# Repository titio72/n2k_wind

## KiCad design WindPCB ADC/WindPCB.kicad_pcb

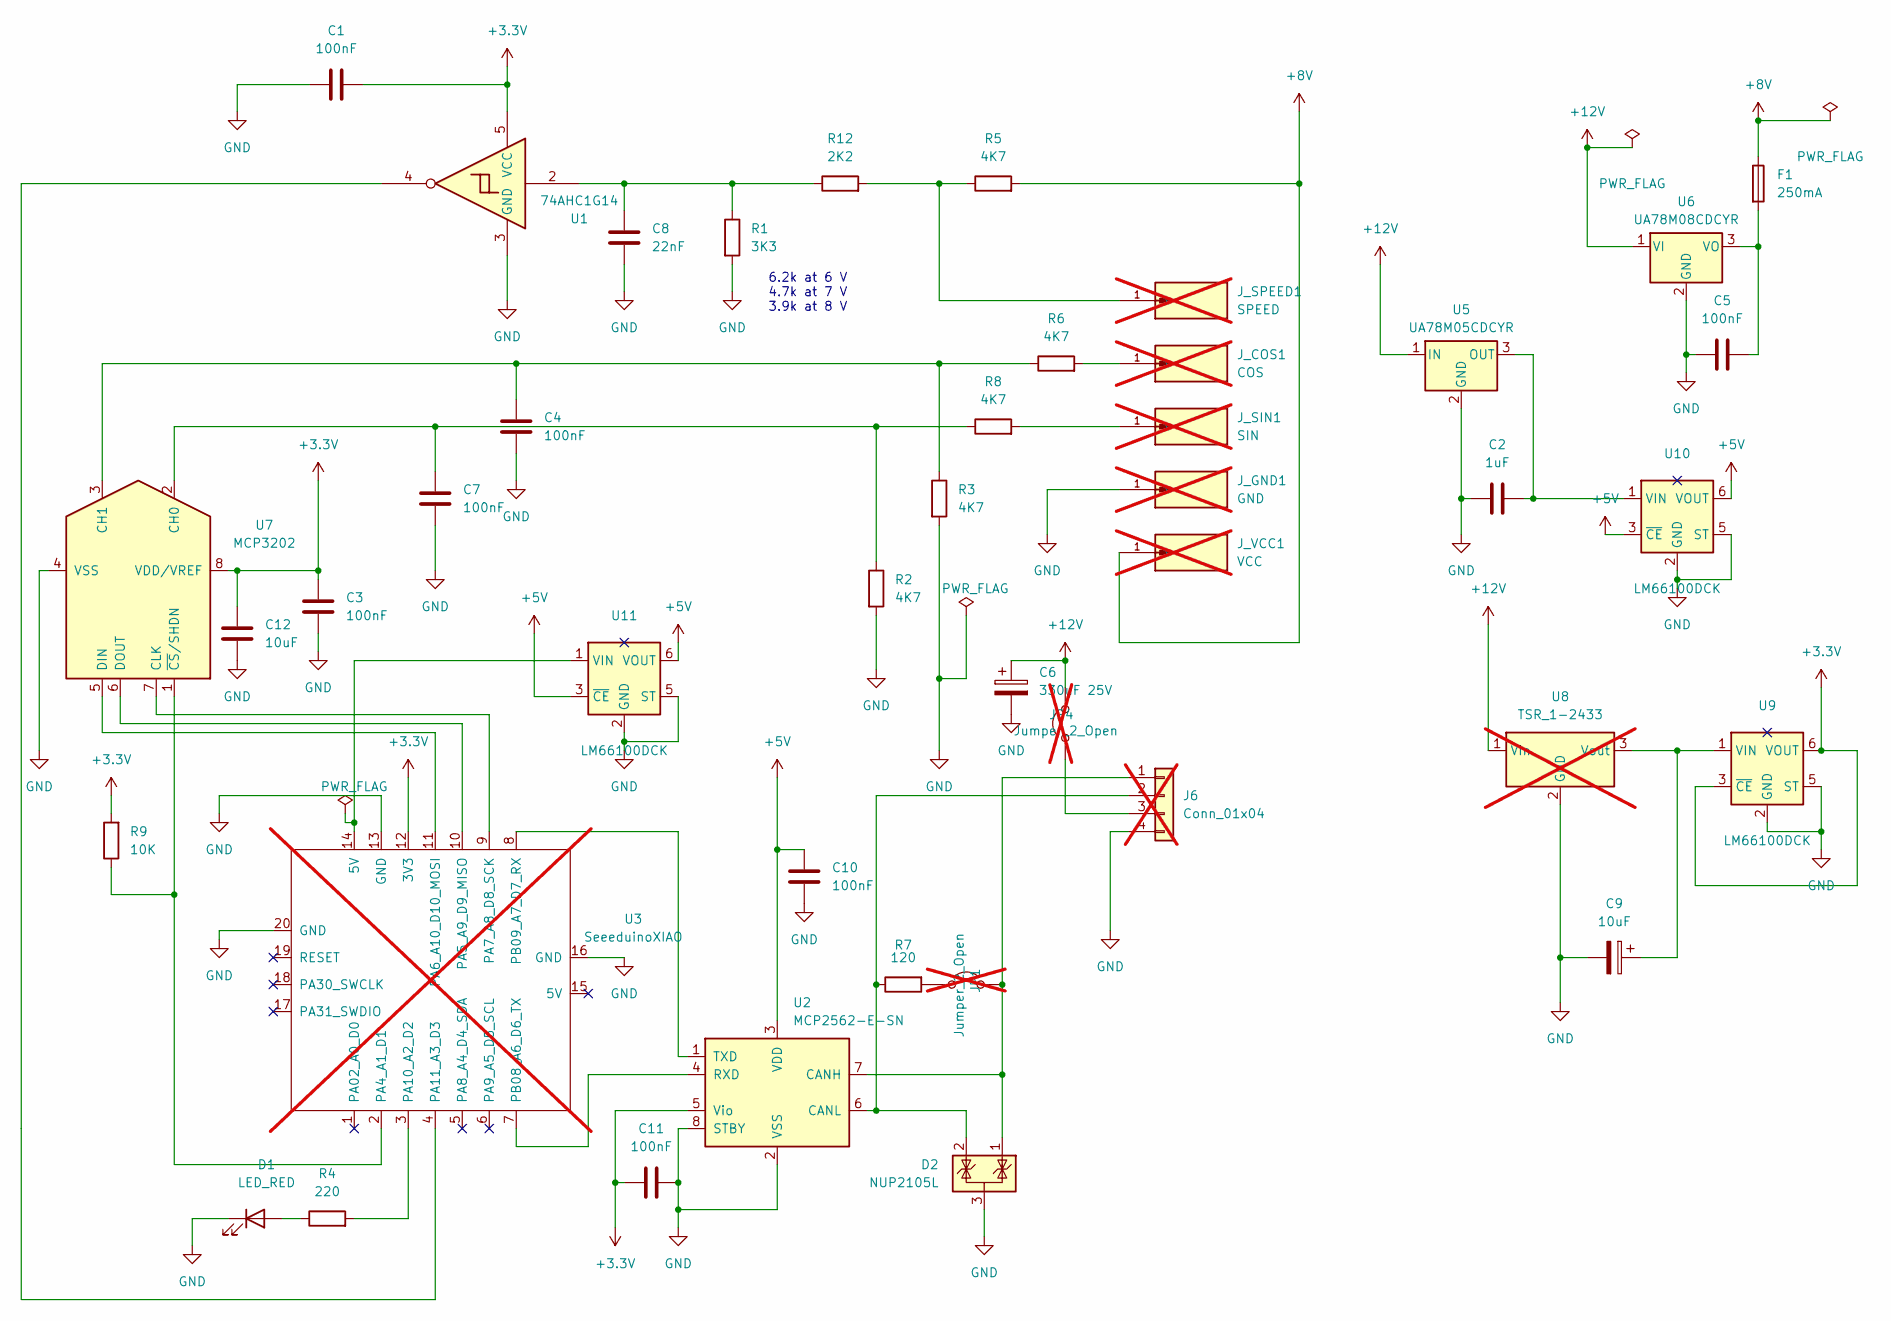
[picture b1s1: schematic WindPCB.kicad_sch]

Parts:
C1, C3, C4, C5, C7, C10, C11: 100nF; C_0805_2012Metric; MPN CC0805KRX7R9BB104
C2: 1uF; C_0805_2012Metric; MPN CC0805KRX7R7BB105
C6: 330uF 25V; CP_Elec_8x10; MPN EEE-FK1E331P
C8: 22nF; C_0805_2012Metric; MPN CC0805KRX7R9BB223
C9: 10uF; CP_EIA-3216-18_Kemet-A; MPN T491A106K010AT
C12: 10uF; C_0805_2012Metric; MPN CL21A106KOQNNNE
D1: LED_RED; LED_0805_2012Metric; MPN 150080RS75000
D2: NUP2105L; SOT-23; MPN NUP2105LT1G
F1: 250mA; Fuse_Littelfuse-NANO2-451_453; MPN 0454.250MR
J6: Conn_01x04; JST_EH_B4B-EH-A_1x04_P2.50mm_Vertical; not fitted
JP1, JP4: Jumper_2_Open; PinHeader_1x02_P2.54mm_Vertical; not fitted
J_COS1: COS; KEYSTONE_1267; PARTREV D; not fitted
J_GND1: GND; KEYSTONE_1267; PARTREV D; not fitted
J_SIN1: SIN; KEYSTONE_1267; PARTREV D; not fitted
J_SPEED1: SPEED; KEYSTONE_1267; PARTREV D; not fitted
J_VCC1: VCC; KEYSTONE_1267; PARTREV D; not fitted
R1: 3K3; R_0805_2012Metric; MPN RC0805FR-073K3L
R2, R3, R5, R6, R8: 4K7; R_0805_2012Metric; MPN RC0805FR-074K7L
R4: 220; R_0805_2012Metric; MPN RC0805FR-07220RL
R7: 120; R_0805_2012Metric; MPN RC0805FR-07120RL
R9: 10K; R_0805_2012Metric; MPN RC0805FR-0710KL
R12: 2K2; R_0805_2012Metric; MPN RC0805FR-072K2L
U1: 74AHC1G14; SOT-23-5_HandSoldering; MPN SN74AHC1G14DBVR
U2: MCP2562-E-SN; SOIC-8_3.9x4.9mm_P1.27mm; MPN MCP2562-E/SN
U3: SeeeduinoXIAO; Seeeduino XIAO-MOUDLE14P-2.54-21X17.8MM_1; not fitted
U5: UA78M05CDCYR; SOT-223-3_TabPin2; MPN UA78M05CDCYR
U6: UA78M08CDCYR; SOT-223-3_TabPin2; MPN UA78M08CDCYR
U7: MCP3202; SOIC-8_3.9x4.9mm_P1.27mm; MPN MCP3202-CI/SN
U8: TSR_1-2433; Converter_DCDC_TRACO_TSR-1_THT; MPN TSR 1-2433; not fitted
U9, U10, U11: LM66100DCK; SOT-363_SC-70-6; MPN LM66100DCKR

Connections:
+3.3V: C1.1, C3.1, C11.1, C12.1, R9.2, U1.5 (VCC), U2.5 (Vio), U3.12 (3V3), U7.8 (VDD/VREF), U9.3 (~CE), U9.6 (VOUT)
+5V: C10.1, U2.3 (VDD), U10.3 (~CE), U10.6 (VOUT), U11.3 (~CE), U11.6 (VOUT)
+8V: F1.1, J_VCC1.1, R5.2
+12V: C6.1, JP4.2 (B), U5.1 (IN), U6.1 (VI), U8.1 (Vin)
GND: C1.2, C2.1, C3.2, C4.2, C5.1, C6.2, C7.2, C8.2, C9.2, C10.2, C11.2, C12.2, D1.1 (K), D2.3 (A), J6.4, J_GND1.1, R1.2, R2.2, R3.2, U1.3 (GND), U2.2 (VSS), U2.8 (STBY), U3.13 (GND), U3.16 (GND), U3.20 (GND), U5.2 (GND), U6.2 (GND), U7.4 (VSS), U8.2 (GND), U9.2 (GND), U9.5 (ST), U10.2 (GND), U10.5 (ST), U11.2 (GND), U11.5 (ST)
unnamed: C8.1, R1.1, R12.1, U1.2
unnamed: D1.2 (A), R4.1
unnamed: D2.1 (K), J6.1, JP1.2 (B), U2.7 (CANH)
unnamed: D2.2 (K), J6.2, R7.1, U2.6 (CANL)
unnamed: J6.3, JP4.1 (A)
unnamed: JP1.1 (A), R7.2
unnamed: J_COS1.1, R6.2
unnamed: J_SIN1.1, R8.2
unnamed: J_SPEED1.1, R5.1, R12.2
unnamed: U2.4 (RXD), U3.7 (PB08_A6_D6_TX)
unnamed: U2.1 (TXD), U3.8 (PB09_A7_D7_RX)
unnamed: R9.1, U3.2 (PA4_A1_D1), U7.1 (~CS/SHDN)
unnamed: U3.10 (PA5_A9_D9_MISO), U7.6 (DOUT)
unnamed: U3.11 (PA6_A10_D10_MOSI), U7.5 (DIN)
unnamed: U3.9 (PA7_A8_D8_SCK), U7.7 (CLK)
unnamed: R4.2, U3.3 (PA10_A2_D2)
unnamed: U1.4, U3.4 (PA11_A3_D3)
unnamed: C5.2, F1.2, U6.3 (VO)
unnamed: C7.1, R2.1, R8.1, U7.2 (CH0)
unnamed: C4.1, R3.1, R6.1, U7.3 (CH1)
unnamed: C9.1, U8.3 (Vout), U9.1 (VIN)
unnamed: C2.2, U5.3 (OUT), U10.1 (VIN)
unnamed: U3.14 (5V), U11.1 (VIN)

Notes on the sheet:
6.2k at 6 V 4.7k at 7 V 3.9k at 8 V

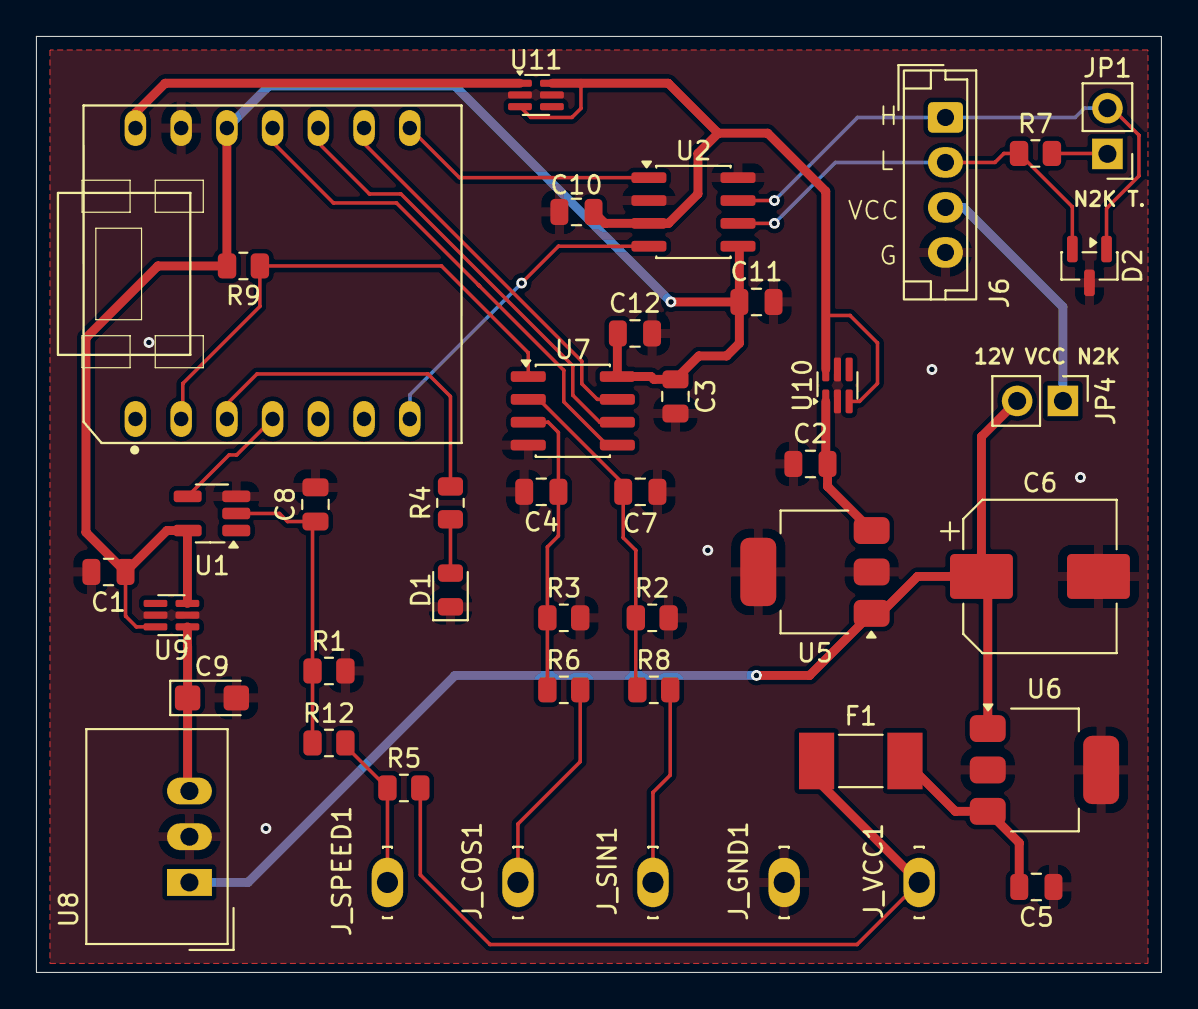
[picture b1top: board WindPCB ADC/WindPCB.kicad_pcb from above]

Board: 2 copper layers, 62.5 x 52.0 mm, 43 parts (0 on the bottom side), 28 nets.

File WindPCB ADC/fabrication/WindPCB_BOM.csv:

"Designator","Value","Footprint","Quantity","MPN","Manufacturer"
"C1, C3, C4, C5, C7, C10, C11","100nF","Capacitor_SMD:C_0805_2012Metric","7","CC0805KRX7R9BB104","Yageo"
"C2","1uF","Capacitor_SMD:C_0805_2012Metric","1","CC0805KRX7R7BB105","Yageo"
"C6","330uF 25V","Capacitor_SMD:CP_Elec_8x10","1","EEE-FK1E331P","Panasonic"
"C8","22nF","Capacitor_SMD:C_0805_2012Metric","1","CC0805KRX7R9BB223","Yageo"
"C9","10uF","Capacitor_Tantalum_SMD:CP_EIA-3216-18_Kemet-A","1","T491A106K010AT","Kemet"
"C12","10uF","Capacitor_SMD:C_0805_2012Metric","1","CL21A106KOQNNNE","Samsung Electro-Mechanics"
"D1","LED_RED","LED_SMD:LED_0805_2012Metric","1","150080RS75000","Wurth Elektronik"
"D2","NUP2105L","Package_TO_SOT_SMD:SOT-23","1","NUP2105LT1G","onsemi"
"F1","250mA","Fuse:Fuse_Littelfuse-NANO2-451_453","1","0454.250MR","Littelfuse"
"R1","3K3","Resistor_SMD:R_0805_2012Metric","1","RC0805FR-073K3L","Yageo"
"R2, R3, R5, R6, R8","4K7","Resistor_SMD:R_0805_2012Metric","5","RC0805FR-074K7L","Yageo"
"R4","220","Resistor_SMD:R_0805_2012Metric","1","RC0805FR-07220RL","Yageo"
"R7","120","Resistor_SMD:R_0805_2012Metric","1","RC0805FR-07120RL","Yageo"
"R9","10K","Resistor_SMD:R_0805_2012Metric","1","RC0805FR-0710KL","Yageo"
"R12","2K2","Resistor_SMD:R_0805_2012Metric","1","RC0805FR-072K2L","Yageo"
"U1","74AHC1G14","Package_TO_SOT_SMD:SOT-23-5_HandSoldering","1","SN74AHC1G14DBVR","Texas Instruments"
"U2","MCP2562-E-SN","Package_SO:SOIC-8_3.9x4.9mm_P1.27mm","1","MCP2562-E/SN","Microchip"
"U5","UA78M05CDCYR","Package_TO_SOT_SMD:SOT-223-3_TabPin2","1","UA78M05CDCYR","Texas Instruments"
"U6","UA78M08CDCYR","Package_TO_SOT_SMD:SOT-223-3_TabPin2","1","UA78M08CDCYR","Texas Instruments"
"U7","MCP3202","Package_SO:SOIC-8_3.9x4.9mm_P1.27mm","1","MCP3202-CI/SN","Microchip"
"U9, U10, U11","LM66100DCK","Package_TO_SOT_SMD:SOT-363_SC-70-6","3","LM66100DCKR","Texas Instruments"

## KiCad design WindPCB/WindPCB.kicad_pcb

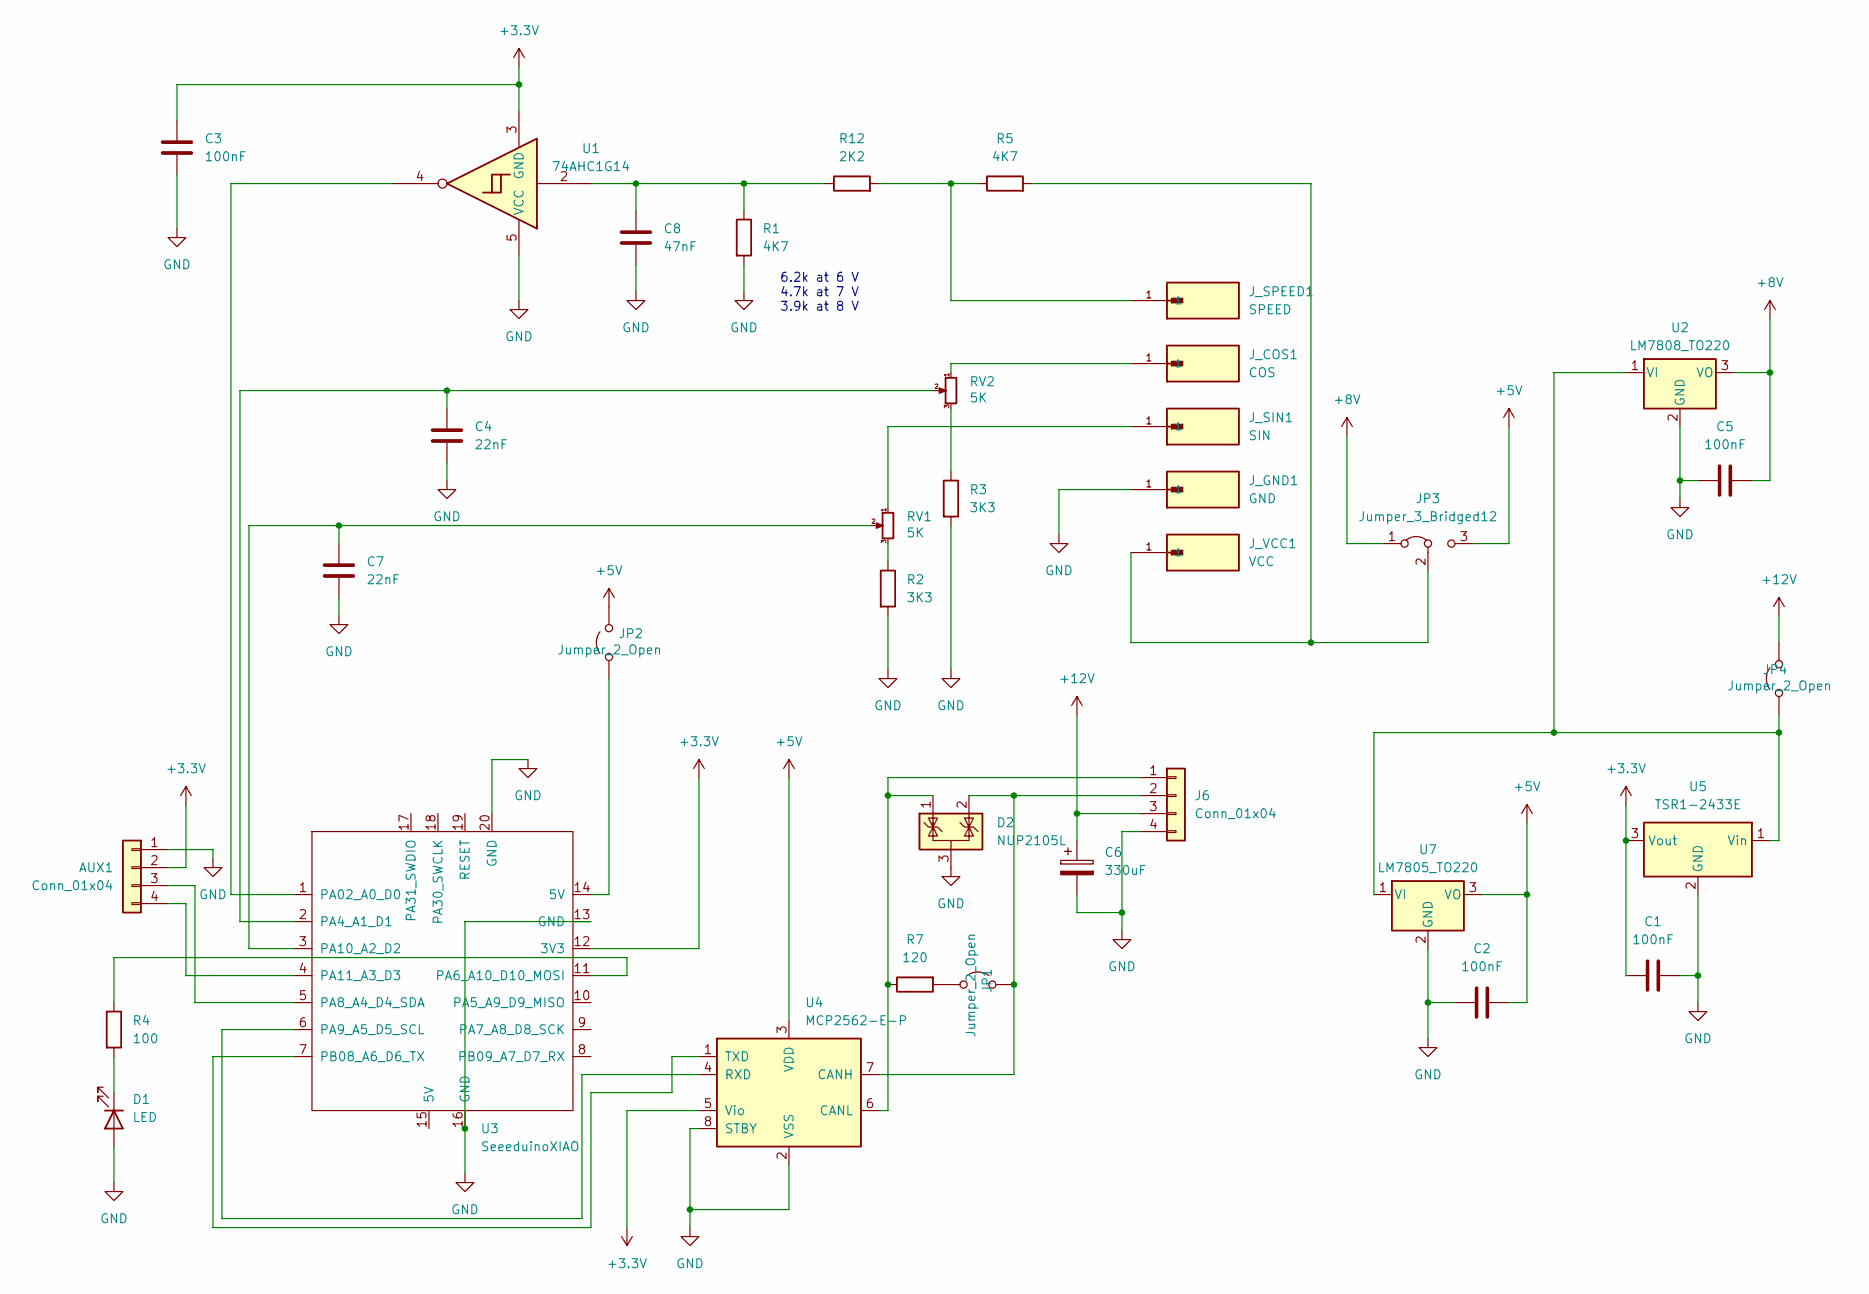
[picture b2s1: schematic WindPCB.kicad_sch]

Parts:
AUX1: Conn_01x04; JST_EH_B4B-EH-A_1x04_P2.50mm_Vertical
C1, C2, C3, C5: 100nF; C_Disc_D6.0mm_W2.5mm_P5.00mm
C4, C7: 22nF; C_Disc_D6.0mm_W2.5mm_P5.00mm
C6: 330uF; CP_Radial_D6.3mm_P2.50mm
C8: 47nF; C_Disc_D6.0mm_W2.5mm_P5.00mm
D1: LED; LED_D3.0mm
D2: NUP2105L; SOT-23
J6: Conn_01x04; JST_EH_B4B-EH-A_1x04_P2.50mm_Vertical
JP1, JP2, JP4: Jumper_2_Open; PinHeader_1x02_P2.54mm_Vertical
JP3: Jumper_3_Bridged12; PinHeader_1x03_P2.54mm_Vertical
J_COS1: COS; KEYSTONE_1267; PARTREV D
J_GND1: GND; KEYSTONE_1267; PARTREV D
J_SIN1: SIN; KEYSTONE_1267; PARTREV D
J_SPEED1: SPEED; KEYSTONE_1267; PARTREV D
J_VCC1: VCC; KEYSTONE_1267; PARTREV D
R1, R5: 4K7; R_Axial_DIN0204_L3.6mm_D1.6mm_P7.62mm_Horizontal
R2, R3: 3K3; R_Axial_DIN0204_L3.6mm_D1.6mm_P7.62mm_Horizontal
R4: 100; R_Axial_DIN0204_L3.6mm_D1.6mm_P7.62mm_Horizontal
R7: 120; R_Axial_DIN0204_L3.6mm_D1.6mm_P7.62mm_Horizontal
R12: 2K2; R_Axial_DIN0204_L3.6mm_D1.6mm_P7.62mm_Horizontal
RV1, RV2: 5K; Potentiometer_Bourns_3296W_Vertical
U1: 74AHC1G14; SOT-23-5_HandSoldering
U2: LM7808_TO220; TO-220-3_Vertical
U3: SeeeduinoXIAO; Seeeduino XIAO-MOUDLE14P-2.54-21X17.8MM_1
U4: MCP2562-E-P; DIP-8_W7.62mm
U5: TSR1-2433E; Converter_DCDC_TRACO_TSR-1_THT
U7: LM7805_TO220; TO-220-3_Vertical

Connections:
+3.3V: AUX1.2, C1.2, C3.1, U1.3 (GND), U3.12 (3V3), U4.5 (Vio), U5.3 (Vout)
+5V: C2.1, JP2.2 (B), JP3.3 (B), U4.3 (VDD), U7.3 (VO)
+8V: C5.1, JP3.1 (A), U2.3 (VO)
+12V: C6.1, J6.3, JP4.2 (B)
GND: AUX1.1, C1.1, C2.2, C3.2, C4.2, C5.2, C6.2, C7.2, C8.2, D1.2 (A), D2.3 (A), J6.4, J_GND1.1, R1.2, R2.2, R3.2, U1.5 (VCC), U2.2 (GND), U3.13 (GND), U3.16 (GND), U3.20 (GND), U4.2 (VSS), U4.8 (STBY), U5.2 (GND), U7.2 (GND)
unnamed: AUX1.3, U3.5 (PA8_A4_D4_SDA)
unnamed: AUX1.4, U3.4 (PA11_A3_D3)
unnamed: C8.1, R1.1, R12.1, U1.2
unnamed: D1.1 (K), R4.2
unnamed: D2.1 (K), J6.1, R7.1, U4.6 (CANL)
unnamed: D2.2 (K), J6.2, JP1.2 (B), U4.7 (CANH)
unnamed: JP1.1 (A), R7.2
unnamed: JP2.1 (A), U3.14 (5V)
unnamed: JP3.2 (C), J_VCC1.1, R5.2
unnamed: JP4.1 (A), U2.1 (VI), U5.1 (Vin), U7.1 (VI)
unnamed: J_COS1.1, RV2.1
unnamed: J_SIN1.1, RV1.1
unnamed: J_SPEED1.1, R5.1, R12.2
unnamed: R2.1, RV1.3
unnamed: R3.1, RV2.3
unnamed: U1.4, U3.1 (PA02_A0_D0)
unnamed: C4.1, RV2.2, U3.2 (PA4_A1_D1)
unnamed: R4.1, U3.11 (PA6_A10_D10_MOSI)
unnamed: U3.6 (PA9_A5_D5_SCL), U4.4 (RXD)
unnamed: C7.1, RV1.2, U3.3 (PA10_A2_D2)
unnamed: U3.7 (PB08_A6_D6_TX), U4.1 (TXD)

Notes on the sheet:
6.2k at 6 V 4.7k at 7 V 3.9k at 8 V

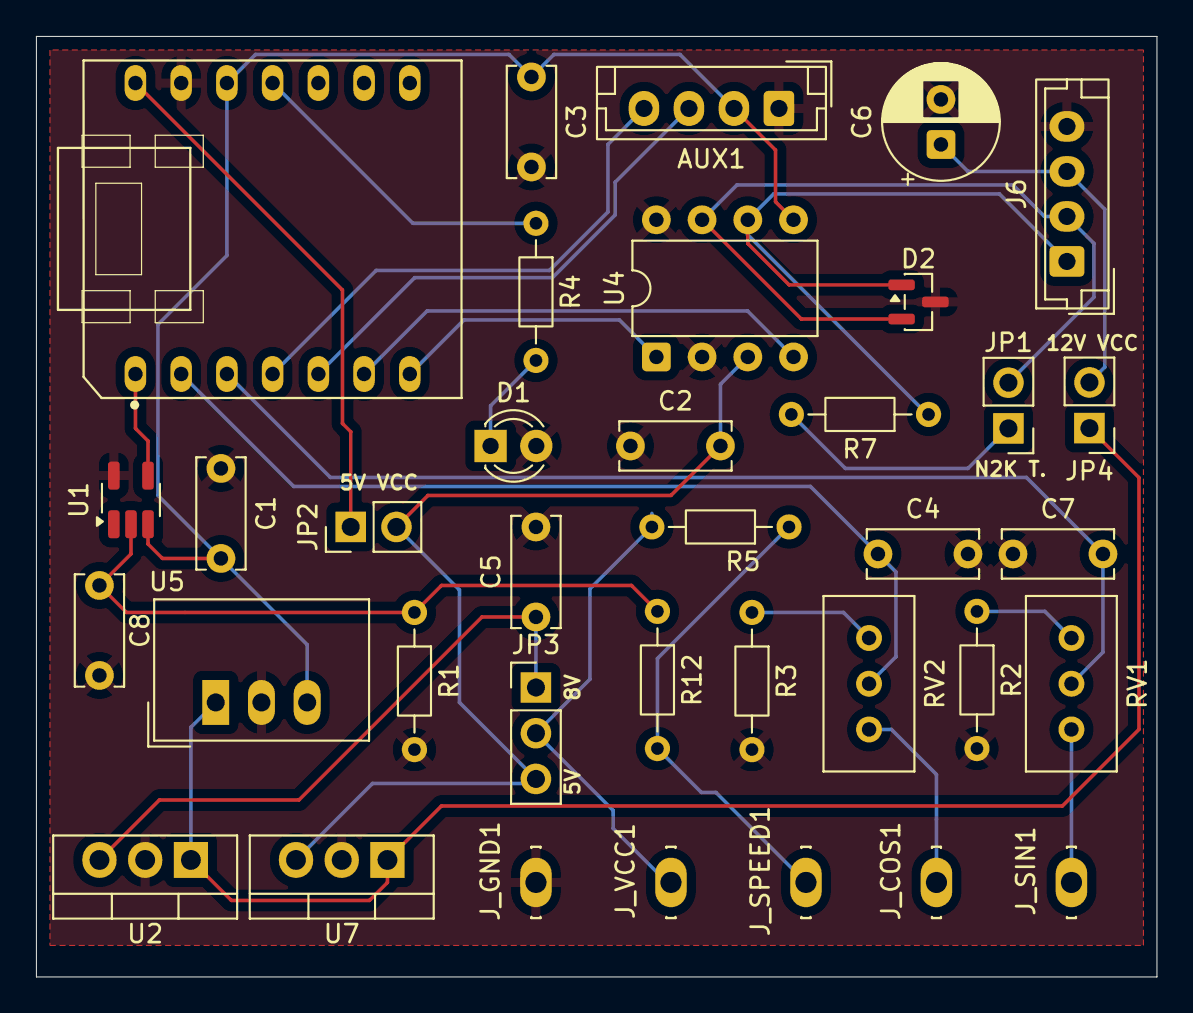
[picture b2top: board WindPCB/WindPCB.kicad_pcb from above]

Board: 2 copper layers, 62.2 x 52.2 mm, 36 parts (0 on the bottom side), 26 nets.

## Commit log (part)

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2024-06-21 Added support for n2k source claim
2024-06-24 refactoring and clean up
2025-10-23 Lot of good stuff
2025-10-27 -WIP: new smoothing startegy - misc
2025-10-30 Added support to auto calibration
2025-11-01 clean up
2025-11-01 Changed analog pins
2025-11-01 remove files not used
2025-11-03 Introduced the concept of calibration score
2025-11-11 Refactoring - added better support for seeed studio esp32
2025-11-12 Added concept of "apply configuration" to uncouple commands and the rest of the app
2025-11-12 added vane type setting added setting to control n2k message frequency (now 2/s)
2025-11-14 Moved BLE constants to Cnstants.h Added delay before starting to collect samples for calibration
2025-11-17 Moved wind_data structure to new module DataAndConf Extended Range object capabilities (expand range & ADC conversion) Eliminated dead code in WindSpeed Minor refactoring of WindDirection: now the Si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
2025-11-18 Vane type is now configurable at runtime and part of the configuration. The code to apply a calibration is now centralized (the CommandHandler "borrows" the callback function from the AutoCalibration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
2025-11-18 Missing commit.
2025-11-23 Removed not used code. Dropeed ADS1115 (not advantages). Added suppoer to change teh device name (BLE). Moved N2K info to Constants. Other minor changes and improvements.
2025-11-24 removed unwanted file
2025-12-17 Refactoring for tests
2026-01-06 Moved libs in a different repository Use tinterrupt to measure frequency in WindSpeed
2026-02-16 Fixed bug where a x2 multplier was used to calculate wind speed. Working on using ADS1115 instead of ESP32 internal ADC.
2026-03-03 Dropped experimental ADS1115 and fixed bug causing frequency to be reported as half of teh real one
2026-06-22 Working on a version using MCP3202m for direction
